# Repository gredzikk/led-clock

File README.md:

A project for Computer Science studies.
Clock consist of round PCB, ATmega328p with MiniCore bootloader driven by 12MHz crystal.
Clock IC is DS3231, time is displayed using 60 LEDs and 4 digit 7 segment display in the middle.
LEDs show seconds, 4digit can display hours, minutes, date, month and year.
Under the display 4 pushbuttons are used to change displayed values and program time.
DS3231 has CR2032 lithium battery power backup for keeping time without clock main power.
LEDs are driven by 8 HC595 shift registers, 4 digit display uses 2 HC595s.
Power is supplied by Liion battery through small 3.7-5V booster alongside with TP4056 charger.

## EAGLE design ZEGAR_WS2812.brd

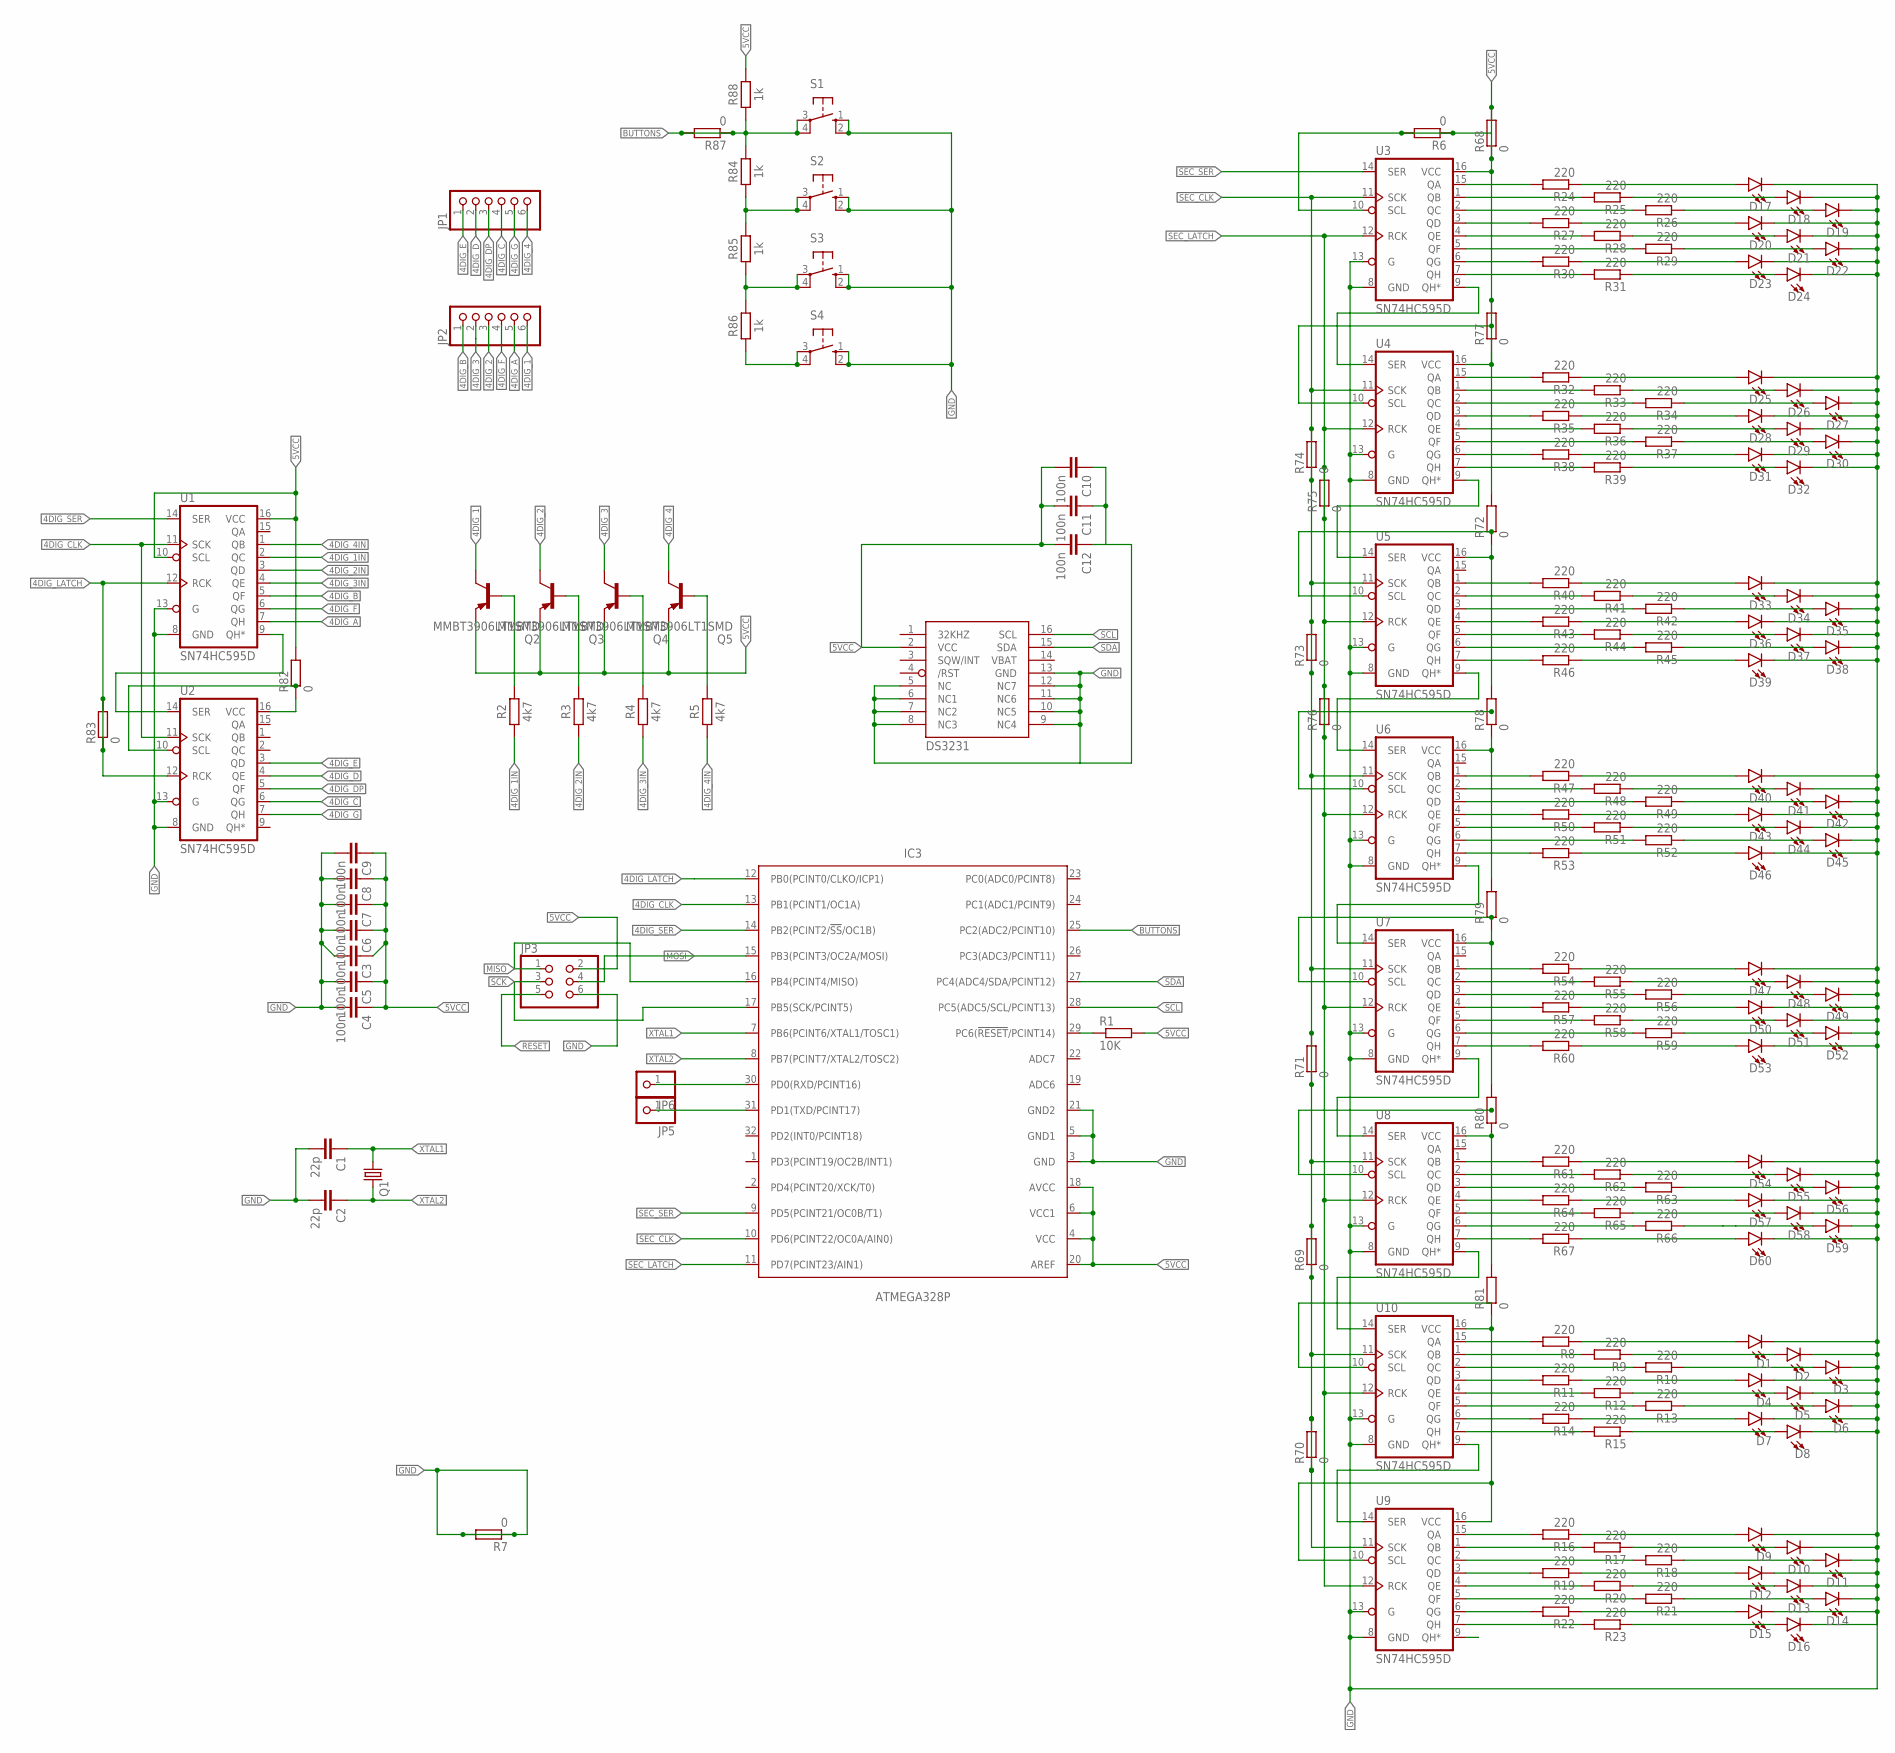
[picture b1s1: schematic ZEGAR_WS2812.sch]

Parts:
C1, C2: 22p; C0805
C3, C4, C5, C6, C7, C8, C9, C10, C11, C12: 100n; C0805
D1, D2, D3, D4, D5, D6, D7, D8, D9, D10, D11, D12, D13, D14, D15, D16, D17, D18, D19, D20, D21, D22, D23, D24, D25, D26, D27, D28, D29, D30, D31, D32, D33, D34, D35, D36, D37, D38, D39, D40, D41, D42, D43, D44, D45, D46, D47, D48, D49, D50, D51, D52, D53, D54, D55, D56, D57, D58, D59, D60: LED3MM; LED_3MM
IC2: DS3231/SO; SO16W
IC3: ATMEGA328P; TQFP32-08
JP1, JP2: PINHD-1X6; 1X06
JP3: PINHD-2X03_2.54-SMD; 2X03SMD
JP5, JP6: PINHD-1X01_2.54-SMD-90°; 1X01SMD/90
Q1: KX-7; 3.2X2.5_KX-7
Q2, Q3, Q4, Q5: MMBT3906LT1SMD; SOT23-BEC
R1: 10K; R0805
R2, R3, R4, R5: 4k7; RESC2012X65
R6, R68, R72, R77, R78, R79, R80, R81, R82, R83, R87: 0; R2512
R7, R69, R70, R71, R73, R74, R75, R76: 0; R1206
R8, R9, R10, R11, R12, R13, R14, R15, R16, R17, R18, R19, R20, R21, R22, R23, R24, R25, R26, R27, R28, R29, R30, R31, R32, R33, R34, R35, R36, R37, R38, R39, R40, R41, R42, R43, R44, R45, R46, R47, R48, R49, R50, R51, R52, R53, R54, R55, R56, R57, R58, R59, R60, R61, R62, R63, R64, R65, R66, R67: 220; R0805
R84, R85, R86, R88: 1k; RESC2012X65
S1, S2, S3, S4: 10-XX; B3F-10XX
U1, U2, U3, U4, U5, U6, U7, U8, U9, U10: SN74HC595D; SO16

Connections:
4DIG_1: JP2.6, Q2.C
4DIG_1IN: R2.1, U1.2 (QC)
4DIG_2: JP2.3, Q3.C
4DIG_2IN: R3.1, U1.3 (QD)
4DIG_3: JP2.2, Q4.C
4DIG_3IN: R4.1, U1.4 (QE)
4DIG_4: JP1.6, Q5.C
4DIG_4IN: R5.1, U1.1 (QB)
4DIG_A: JP2.5, U1.7 (QH)
4DIG_B: JP2.1, U1.5 (QF)
4DIG_C: JP1.4, U2.6 (QG)
4DIG_CLK: IC3.13 (PB1(PCINT1/OC1A)), U1.11 (SCK), U2.11 (SCK)
4DIG_D: JP1.2, U2.4 (QE)
4DIG_DP: JP1.3, U2.5 (QF)
4DIG_E: JP1.1, U2.3 (QD)
4DIG_F: JP2.4, U1.6 (QG)
4DIG_G: JP1.5, U2.7 (QH)
4DIG_LATCH: IC3.12 (PB0(PCINT0/CLKO/ICP1)), R83.1, R83.2, U1.12 (RCK), U2.12 (RCK)
4DIG_SER: IC3.14 (PB2(PCINT2/!SS!/OC1B)), U1.14 (SER)
5VCC: C3.1, C4.1, C5.1, C6.1, C7.1, C8.1, C9.1, C10.2, C11.2, C12.2, IC2.2 (VCC), IC3.4 (VCC), IC3.6 (VCC1), IC3.18 (AVCC), IC3.20 (AREF), JP3.2, Q2.E, Q3.E, Q4.E, Q5.E, R1.2, R6.1, R6.2, R68.1, R68.2, R72.1, R72.2, R77.1, R77.2, R78.1, R78.2, R79.1, R79.2, R80.1, R80.2, R81.1, R81.2, R82.1, R82.2, R88.2, U1.10 (SCL), U1.16 (VCC), U2.10 (SCL), U2.16 (VCC), U3.10 (SCL), U3.16 (VCC), U4.10 (SCL), U4.16 (VCC), U5.10 (SCL), U5.16 (VCC), U6.10 (SCL), U6.16 (VCC), U7.10 (SCL), U7.16 (VCC), U8.10 (SCL), U8.16 (VCC), U9.10 (SCL), U9.16 (VCC), U10.10 (SCL), U10.16 (VCC)
BUTTONS: IC3.25 (PC2(ADC2/PCINT10)), R84.2, R87.1, R87.2, R88.1, S1.3, S1.4 (P1)
GND: C1.2, C2.2, C3.2, C4.2, C5.2, C6.2, C7.2, C8.2, C9.2, C10.1, C11.1, C12.1, D1.K (C), D2.K (C), D3.K (C), D4.K (C), D5.K (C), D6.K (C), D7.K (C), D8.K (C), D9.K (C), D10.K (C), D11.K (C), D12.K (C), D13.K (C), D14.K (C), D15.K (C), D16.K (C), D17.K (C), D18.K (C), D19.K (C), D20.K (C), D21.K (C), D22.K (C), D23.K (C), D24.K (C), D25.K (C), D26.K (C), D27.K (C), D28.K (C), D29.K (C), D30.K (C), D31.K (C), D32.K (C), D33.K (C), D34.K (C), D35.K (C), D36.K (C), D37.K (C), D38.K (C), D39.K (C), D40.K (C), D41.K (C), D42.K (C), D43.K (C), D44.K (C), D45.K (C), D46.K (C), D47.K (C), D48.K (C), D49.K (C), D50.K (C), D51.K (C), D52.K (C), D53.K (C), D54.K (C), D55.K (C), D56.K (C), D57.K (C), D58.K (C), D59.K (C), D60.K (C), IC2.5 (NC), IC2.6 (NC1), IC2.7 (NC2), IC2.8 (NC3), IC2.9 (NC4), IC2.10 (NC5), IC2.11 (NC6), IC2.12 (NC7), IC2.13 (GND), IC3.3 (GND), IC3.5 (GND1), IC3.21 (GND2), JP3.6, R7.1, R7.2, S1.1 (S), S1.2 (S1), S2.1 (S), S2.2 (S1), S3.1 (S), S3.2 (S1), S4.1 (S), S4.2 (S1), U1.8 (GND), U1.13 (G), U2.8 (GND), U2.13 (G), U3.8 (GND), U3.13 (G), U4.8 (GND), U4.13 (G), U5.8 (GND), U5.13 (G), U6.8 (GND), U6.13 (G), U7.8 (GND), U7.13 (G), U8.8 (GND), U8.13 (G), U9.8 (GND), U9.13 (G), U10.8 (GND), U10.13 (G)
MISO: IC3.16 (PB4(PCINT4/MISO)), JP3.1
MOSI: IC3.15 (PB3(PCINT3/OC2A/MOSI)), JP3.4
unnamed: U1.9 (QH*), U2.14 (SER)
unnamed: U9.14 (SER), U10.9 (QH*)
unnamed: R8.2, U10.15 (QA)
unnamed: R9.2, U10.1 (QB)
unnamed: R10.2, U10.2 (QC)
unnamed: R11.2, U10.3 (QD)
unnamed: R12.2, U10.4 (QE)
unnamed: R13.2, U10.5 (QF)
unnamed: U7.9 (QH*), U8.14 (SER)
unnamed: U6.9 (QH*), U7.14 (SER)
unnamed: U5.9 (QH*), U6.14 (SER)
unnamed: U4.9 (QH*), U5.14 (SER)
unnamed: U3.9 (QH*), U4.14 (SER)
unnamed: R14.2, U10.6 (QG)
unnamed: R15.2, U10.7 (QH)
unnamed: R16.2, U9.15 (QA)
unnamed: Q2.B, R2.2
unnamed: Q3.B, R3.2
unnamed: Q4.B, R4.2
unnamed: Q5.B, R5.2
unnamed: R17.2, U9.1 (QB)
unnamed: R18.2, U9.2 (QC)
unnamed: R19.2, U9.3 (QD)
unnamed: R20.2, U9.4 (QE)
unnamed: R21.2, U9.5 (QF)
unnamed: R22.2, U9.6 (QG)
unnamed: R23.2, U9.7 (QH)
unnamed: R24.2, U3.15 (QA)
unnamed: R25.2, U3.1 (QB)
unnamed: R26.2, U3.2 (QC)
unnamed: R27.2, U3.3 (QD)
unnamed: R28.2, U3.4 (QE)
unnamed: R29.2, U3.5 (QF)
unnamed: R30.2, U3.6 (QG)
unnamed: R31.2, U3.7 (QH)
unnamed: R32.2, U4.15 (QA)
unnamed: R33.2, U4.1 (QB)
unnamed: R34.2, U4.2 (QC)
unnamed: R35.2, U4.3 (QD)
unnamed: R36.2, U4.4 (QE)
unnamed: R37.2, U4.5 (QF)
unnamed: R38.2, U4.6 (QG)
unnamed: R39.2, U4.7 (QH)
unnamed: R47.2, U6.1 (QB)
unnamed: R40.2, U5.1 (QB)
unnamed: R41.2, U5.2 (QC)
unnamed: R42.2, U5.3 (QD)
unnamed: R43.2, U5.4 (QE)
unnamed: R44.2, U5.5 (QF)
unnamed: R45.2, U5.6 (QG)
unnamed: R46.2, U5.7 (QH)
unnamed: R48.2, U6.2 (QC)
unnamed: R49.2, U6.3 (QD)
unnamed: R50.2, U6.4 (QE)
unnamed: R51.2, U6.5 (QF)
unnamed: R52.2, U6.6 (QG)
unnamed: R53.2, U6.7 (QH)
unnamed: R54.2, U7.1 (QB)
unnamed: R55.2, U7.2 (QC)
unnamed: R56.2, U7.3 (QD)
unnamed: R57.2, U7.4 (QE)
unnamed: R58.2, U7.5 (QF)
unnamed: R59.2, U7.6 (QG)
unnamed: R60.2, U7.7 (QH)
unnamed: R61.2, U8.1 (QB)
unnamed: R62.2, U8.2 (QC)
unnamed: R63.2, U8.3 (QD)
unnamed: R64.2, U8.4 (QE)
unnamed: R65.2, U8.5 (QF)
unnamed: R66.2, U8.6 (QG)
unnamed: R67.2, U8.7 (QH)
unnamed: D1.A, R8.1
unnamed: D2.A, R9.1
unnamed: D4.A, R11.1
unnamed: D3.A, R10.1
unnamed: D7.A, R14.1
unnamed: D5.A, R12.1
unnamed: D6.A, R13.1
unnamed: D8.A, R15.1
unnamed: D9.A, R16.1
unnamed: D12.A, R19.1
unnamed: D15.A, R22.1
unnamed: D17.A, R24.1
unnamed: D18.A, R25.1
unnamed: D19.A, R26.1
unnamed: D10.A, R17.1
unnamed: D13.A, R20.1
unnamed: D11.A, R18.1
unnamed: D16.A, R23.1
unnamed: D14.A, R21.1
unnamed: D23.A, R30.1
unnamed: D22.A, R29.1
unnamed: D21.A, R28.1
unnamed: D20.A, R27.1
unnamed: D24.A, R31.1
unnamed: D25.A, R32.1
unnamed: D26.A, R33.1
unnamed: D27.A, R34.1
unnamed: D28.A, R35.1
unnamed: D29.A, R36.1
unnamed: D30.A, R37.1
unnamed: D31.A, R38.1
unnamed: D32.A, R39.1
unnamed: D33.A, R40.1
unnamed: D34.A, R41.1
unnamed: D35.A, R42.1
unnamed: D36.A, R43.1
unnamed: D37.A, R44.1
unnamed: D38.A, R45.1
unnamed: D39.A, R46.1
unnamed: D40.A, R47.1
unnamed: D41.A, R48.1
unnamed: D42.A, R49.1
unnamed: D43.A, R50.1
unnamed: D44.A, R51.1
unnamed: D45.A, R52.1
unnamed: D46.A, R53.1
unnamed: D47.A, R54.1
unnamed: D48.A, R55.1
unnamed: D49.A, R56.1
unnamed: D50.A, R57.1
unnamed: D51.A, R58.1
unnamed: D52.A, R59.1
unnamed: D53.A, R60.1
unnamed: D54.A, R61.1
unnamed: D55.A, R62.1
unnamed: D56.A, R63.1
unnamed: D57.A, R64.1
unnamed: D60.A, R67.1
unnamed: D59.A, R66.1
unnamed: D58.A, R65.1
unnamed: IC3.30 (PD0(RXD/PCINT16)), JP6.1
unnamed: IC3.31 (PD1(TXD/PCINT17)), JP5.1
unnamed: R84.1, R85.2, S2.3, S2.4 (P1)
unnamed: R85.1, R86.2, S3.3, S3.4 (P1)
unnamed: R86.1, S4.3, S4.4 (P1)
RESET: IC3.29 (PC6(!RESET!/PCINT14)), JP3.5, R1.1
SCK: IC3.17 (PB5(SCK/PCINT5)), JP3.3
SCL: IC2.16 (SCL), IC3.28 (PC5(ADC5/SCL/PCINT13))
SDA: IC2.15 (SDA), IC3.27 (PC4(ADC4/SDA/PCINT12))
SEC_CLK: IC3.10 (PD6(PCINT22/OC0A/AIN0)), R69.1, R69.2, R70.1, R70.2, R71.1, R71.2, R73.1, R73.2, R74.1, R74.2, U3.11 (SCK), U4.11 (SCK), U5.11 (SCK), U6.11 (SCK), U7.11 (SCK), U8.11 (SCK), U9.11 (SCK), U10.11 (SCK)
SEC_LATCH: IC3.11 (PD7(PCINT23/AIN1)), R75.1, R75.2, R76.1, R76.2, U3.12 (RCK), U4.12 (RCK), U5.12 (RCK), U6.12 (RCK), U7.12 (RCK), U8.12 (RCK), U9.12 (RCK), U10.12 (RCK)
SEC_SER: IC3.9 (PD5(PCINT21/OC0B/T1)), U3.14 (SER)
SEC_SERIAL: U8.9 (QH*), U10.14 (SER)
VBAT: IC2.14 (VBAT)
XTAL1: C1.1, IC3.7 (PB6(PCINT6/XTAL1/TOSC1)), Q1.1
XTAL2: C2.1, IC3.8 (PB7(PCINT7/XTAL2/TOSC2)), Q1.3 (2)

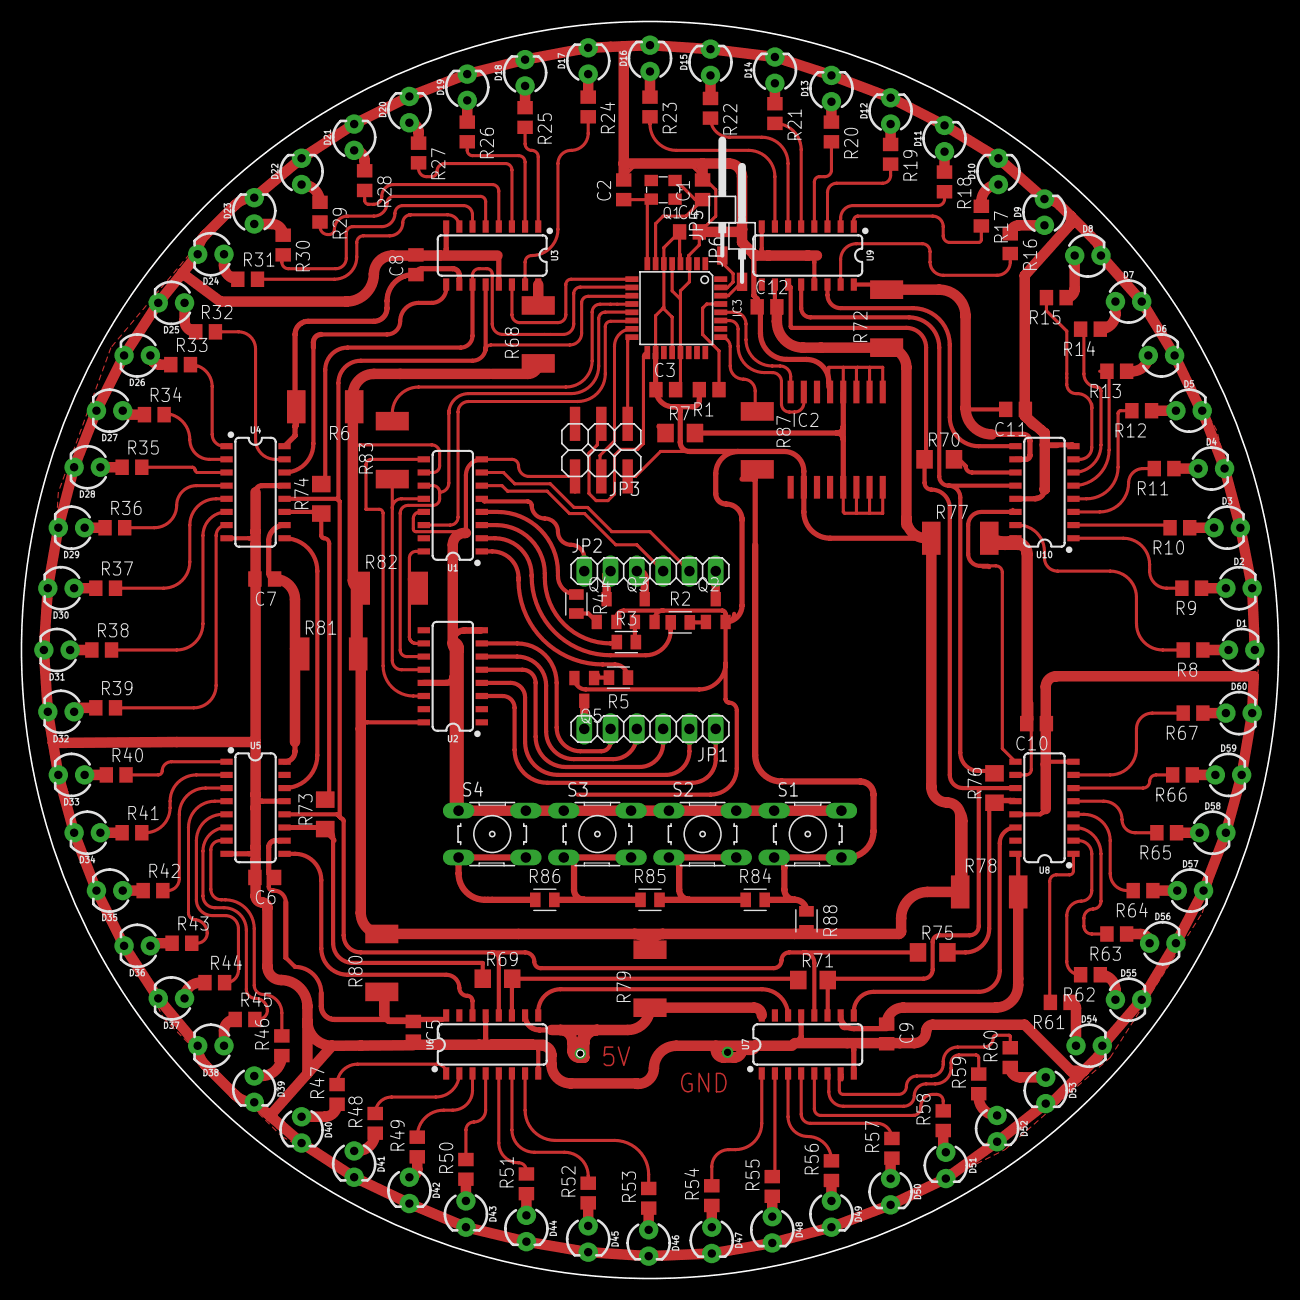
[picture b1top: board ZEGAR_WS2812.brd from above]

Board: 2 copper layers, 121.4 x 121.4 mm, 186 parts (0 on the bottom side), 170 nets.

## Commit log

2023-11-27 all elements in place
2023-11-27 fixed hc595 posiiton
2023-11-28 placed traces from diodes to shift registers
2023-11-28 hc595 for seconds completed
2023-11-30 almost done
2023-11-30 done?
2023-11-30 added programming pins and rx tx pins
2023-11-30 adjusted some traces
2023-12-08 Rename ZEGAR_WS2812.b#1 to eagle/ZEGAR_WS2812.b#1
2023-12-08 Rename ZEGAR_WS2812.b#2 to eagle/ZEGAR_WS2812.b#2
2023-12-08 Rename ZEGAR_WS2812.b#3 to eagle/ZEGAR_WS2812.b#3
2023-12-08 Rename ZEGAR_WS2812.b#4 to eagle/ZEGAR_WS2812.b#4
2023-12-08 Rename ZEGAR_WS2812.b#5 to eagle/ZEGAR_WS2812.b#5
2023-12-08 Rename ZEGAR_WS2812.b#6 to eagle/ZEGAR_WS2812.b#6
2023-12-08 Rename ZEGAR_WS2812.b#7 to eagle/ZEGAR_WS2812.b#7
2023-12-08 Rename ZEGAR_WS2812.b#8 to eagle/ZEGAR_WS2812.b#8
2023-12-08 Rename ZEGAR_WS2812.b#9 to eagle/ZEGAR_WS2812.b#9
2023-12-08 Rename ZEGAR_WS2812.brd to eagle/ZEGAR_WS2812.brd
2023-12-08 Rename ZEGAR_WS2812.s#1 to eagle/ZEGAR_WS2812.s#1
2023-12-08 Rename ZEGAR_WS2812.s#2 to eagle/ZEGAR_WS2812.s#2
2023-12-08 Rename ZEGAR_WS2812.s#3 to eagle/ZEGAR_WS2812.s#3
2023-12-08 Rename ZEGAR_WS2812.s#4 to eagle/ZEGAR_WS2812.s#4
2023-12-08 Rename ZEGAR_WS2812.s#5 to eagle/ZEGAR_WS2812.s#5
2023-12-08 Rename ZEGAR_WS2812.s#6 to eagle/ZEGAR_WS2812.s#6
2023-12-08 Rename ZEGAR_WS2812.s#7 to eagle/ZEGAR_WS2812.s#7
2023-12-08 Update and rename ZEGAR_WS2812.s#8 to eagle/ZEGAR_WS2812.s#8
2023-12-08 Update and rename ZEGAR_WS2812.s#9 to eagle/ZEGAR_WS2812.s#9
2023-12-08 Rename ZEGAR_WS2812.sch to eagle/ZEGAR_WS2812.sch
2023-12-08 Rename eagle.epf to eagle/eagle.epf
2023-12-08 working 7seg 4digit display
2024-01-26 Added description

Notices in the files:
parts and their libraries:
crystal-geyer_V1_0: Copyright: Geyer-Electronic
SparkFun-IC-Logic: Licensing: Creative Commons ShareAlike 4.0 International - https://creativecommons.org/licenses/by-sa/4.0
